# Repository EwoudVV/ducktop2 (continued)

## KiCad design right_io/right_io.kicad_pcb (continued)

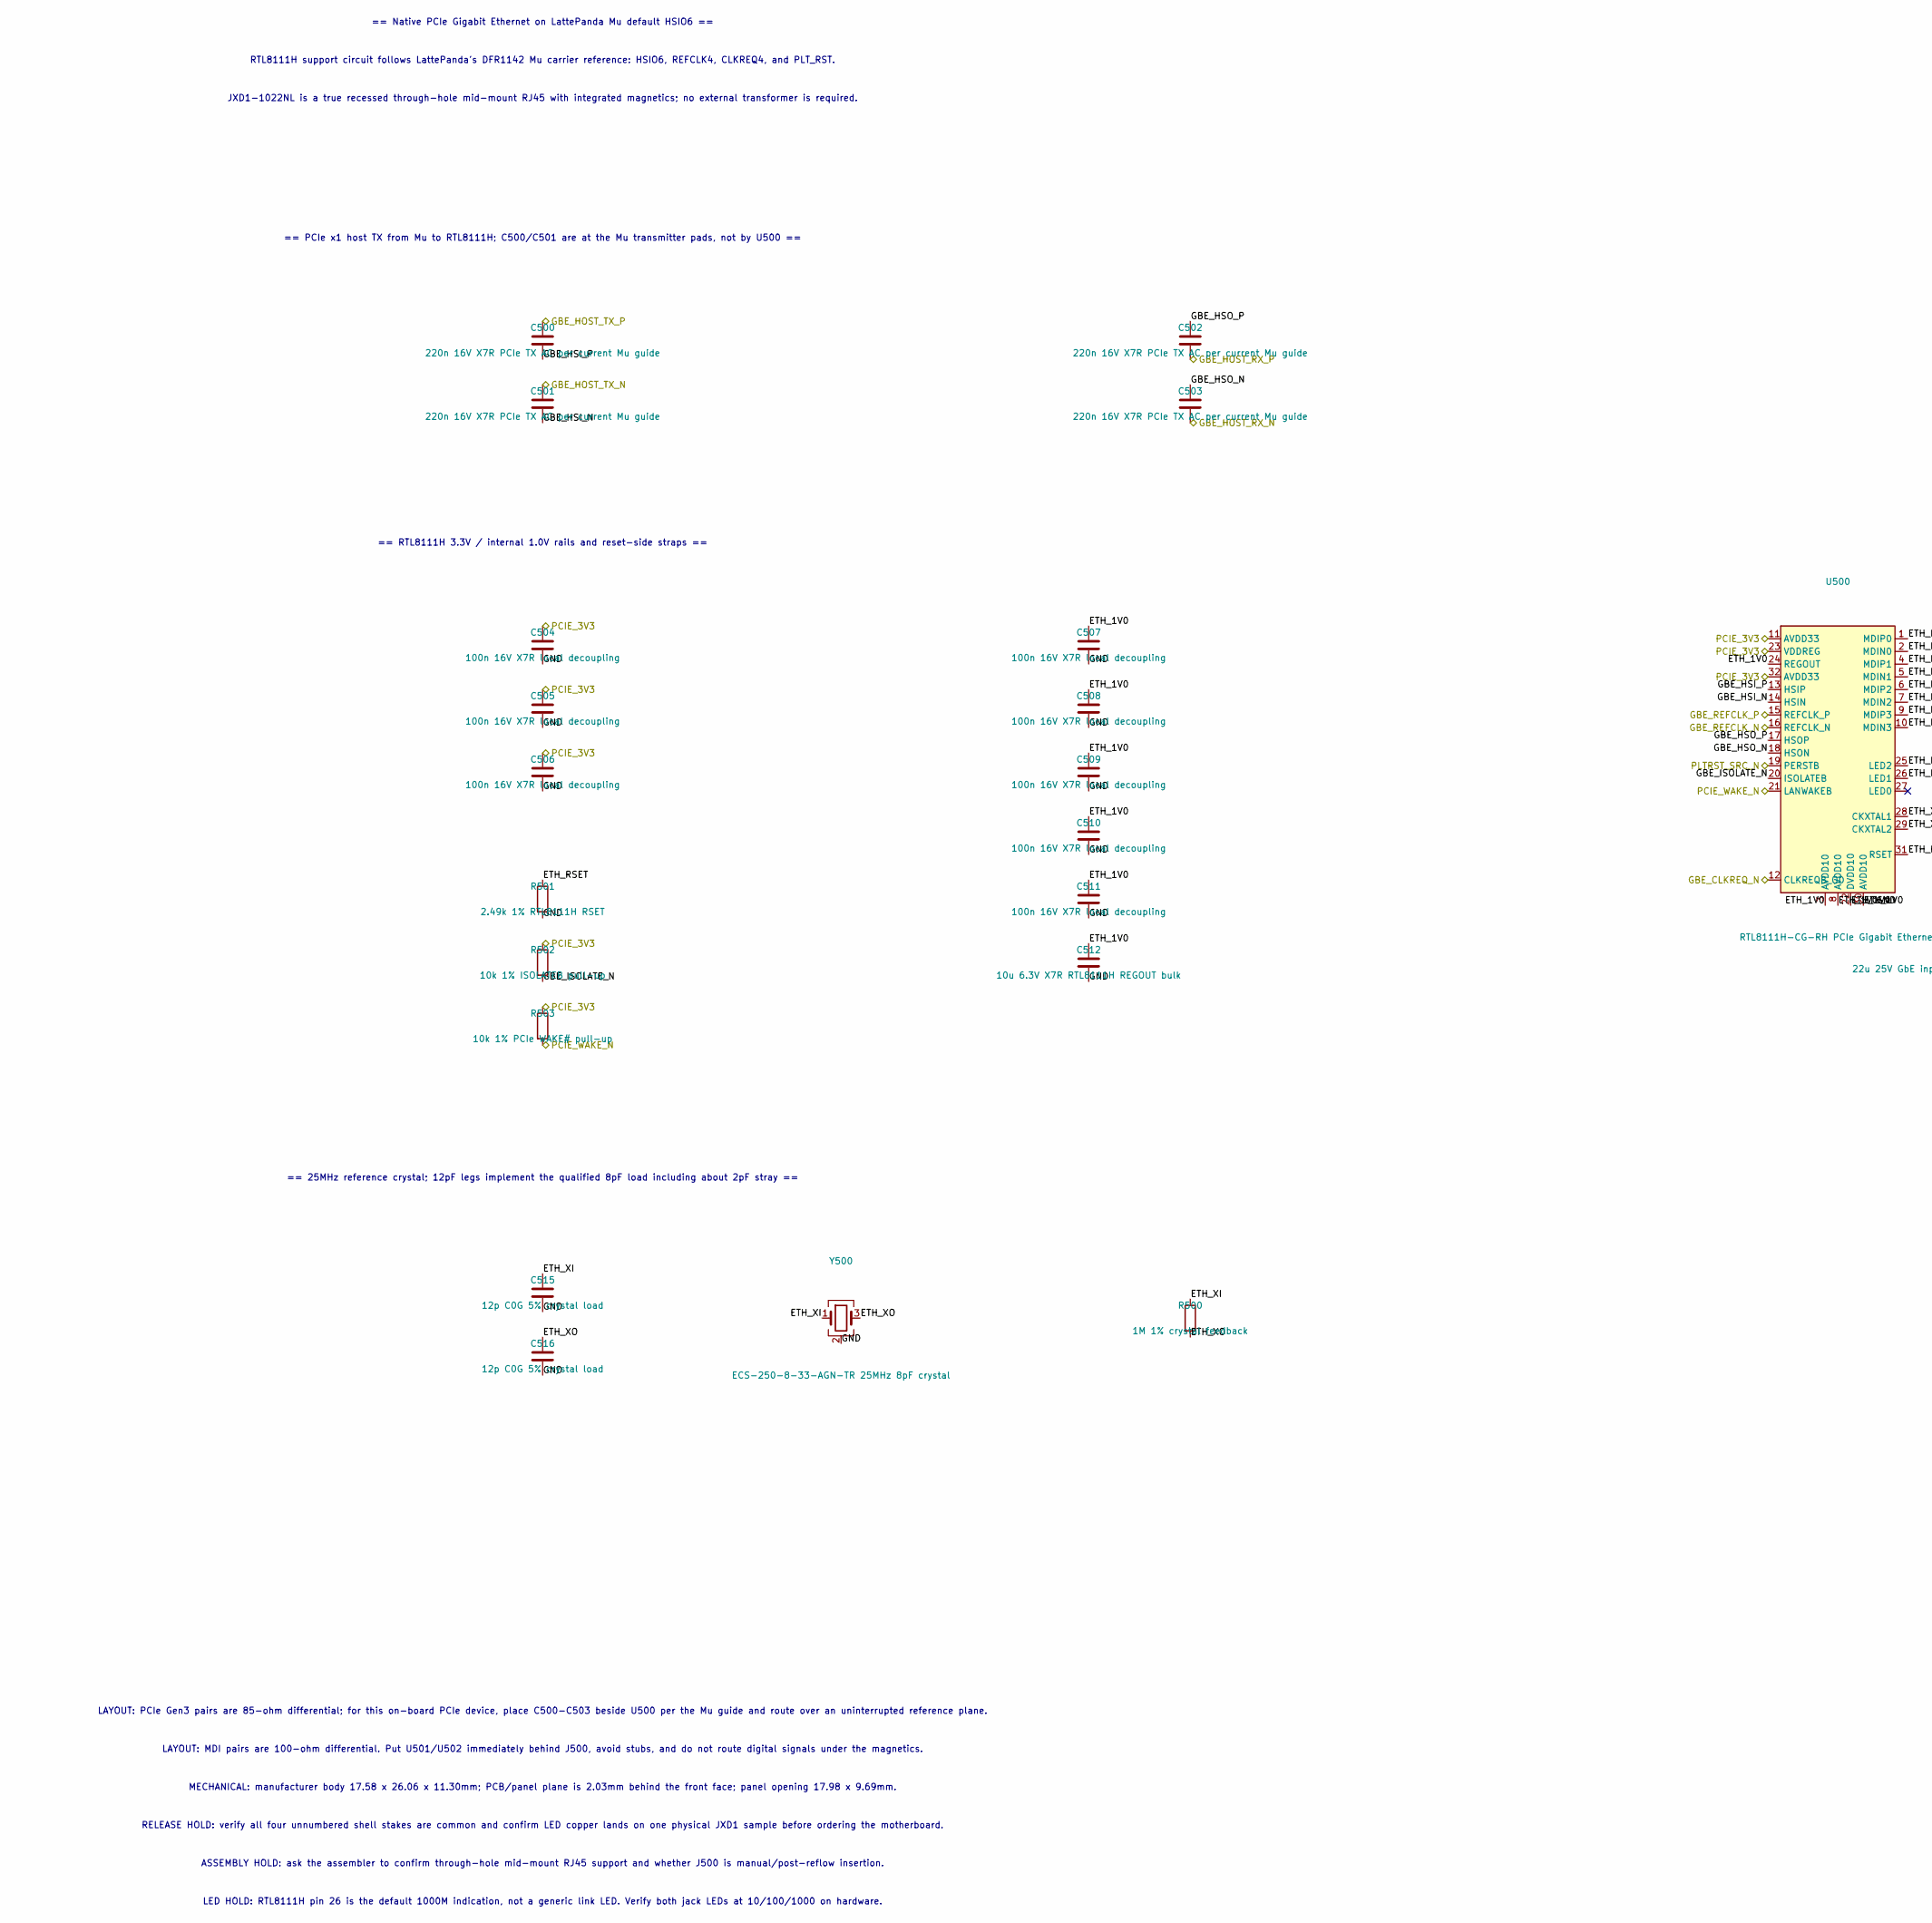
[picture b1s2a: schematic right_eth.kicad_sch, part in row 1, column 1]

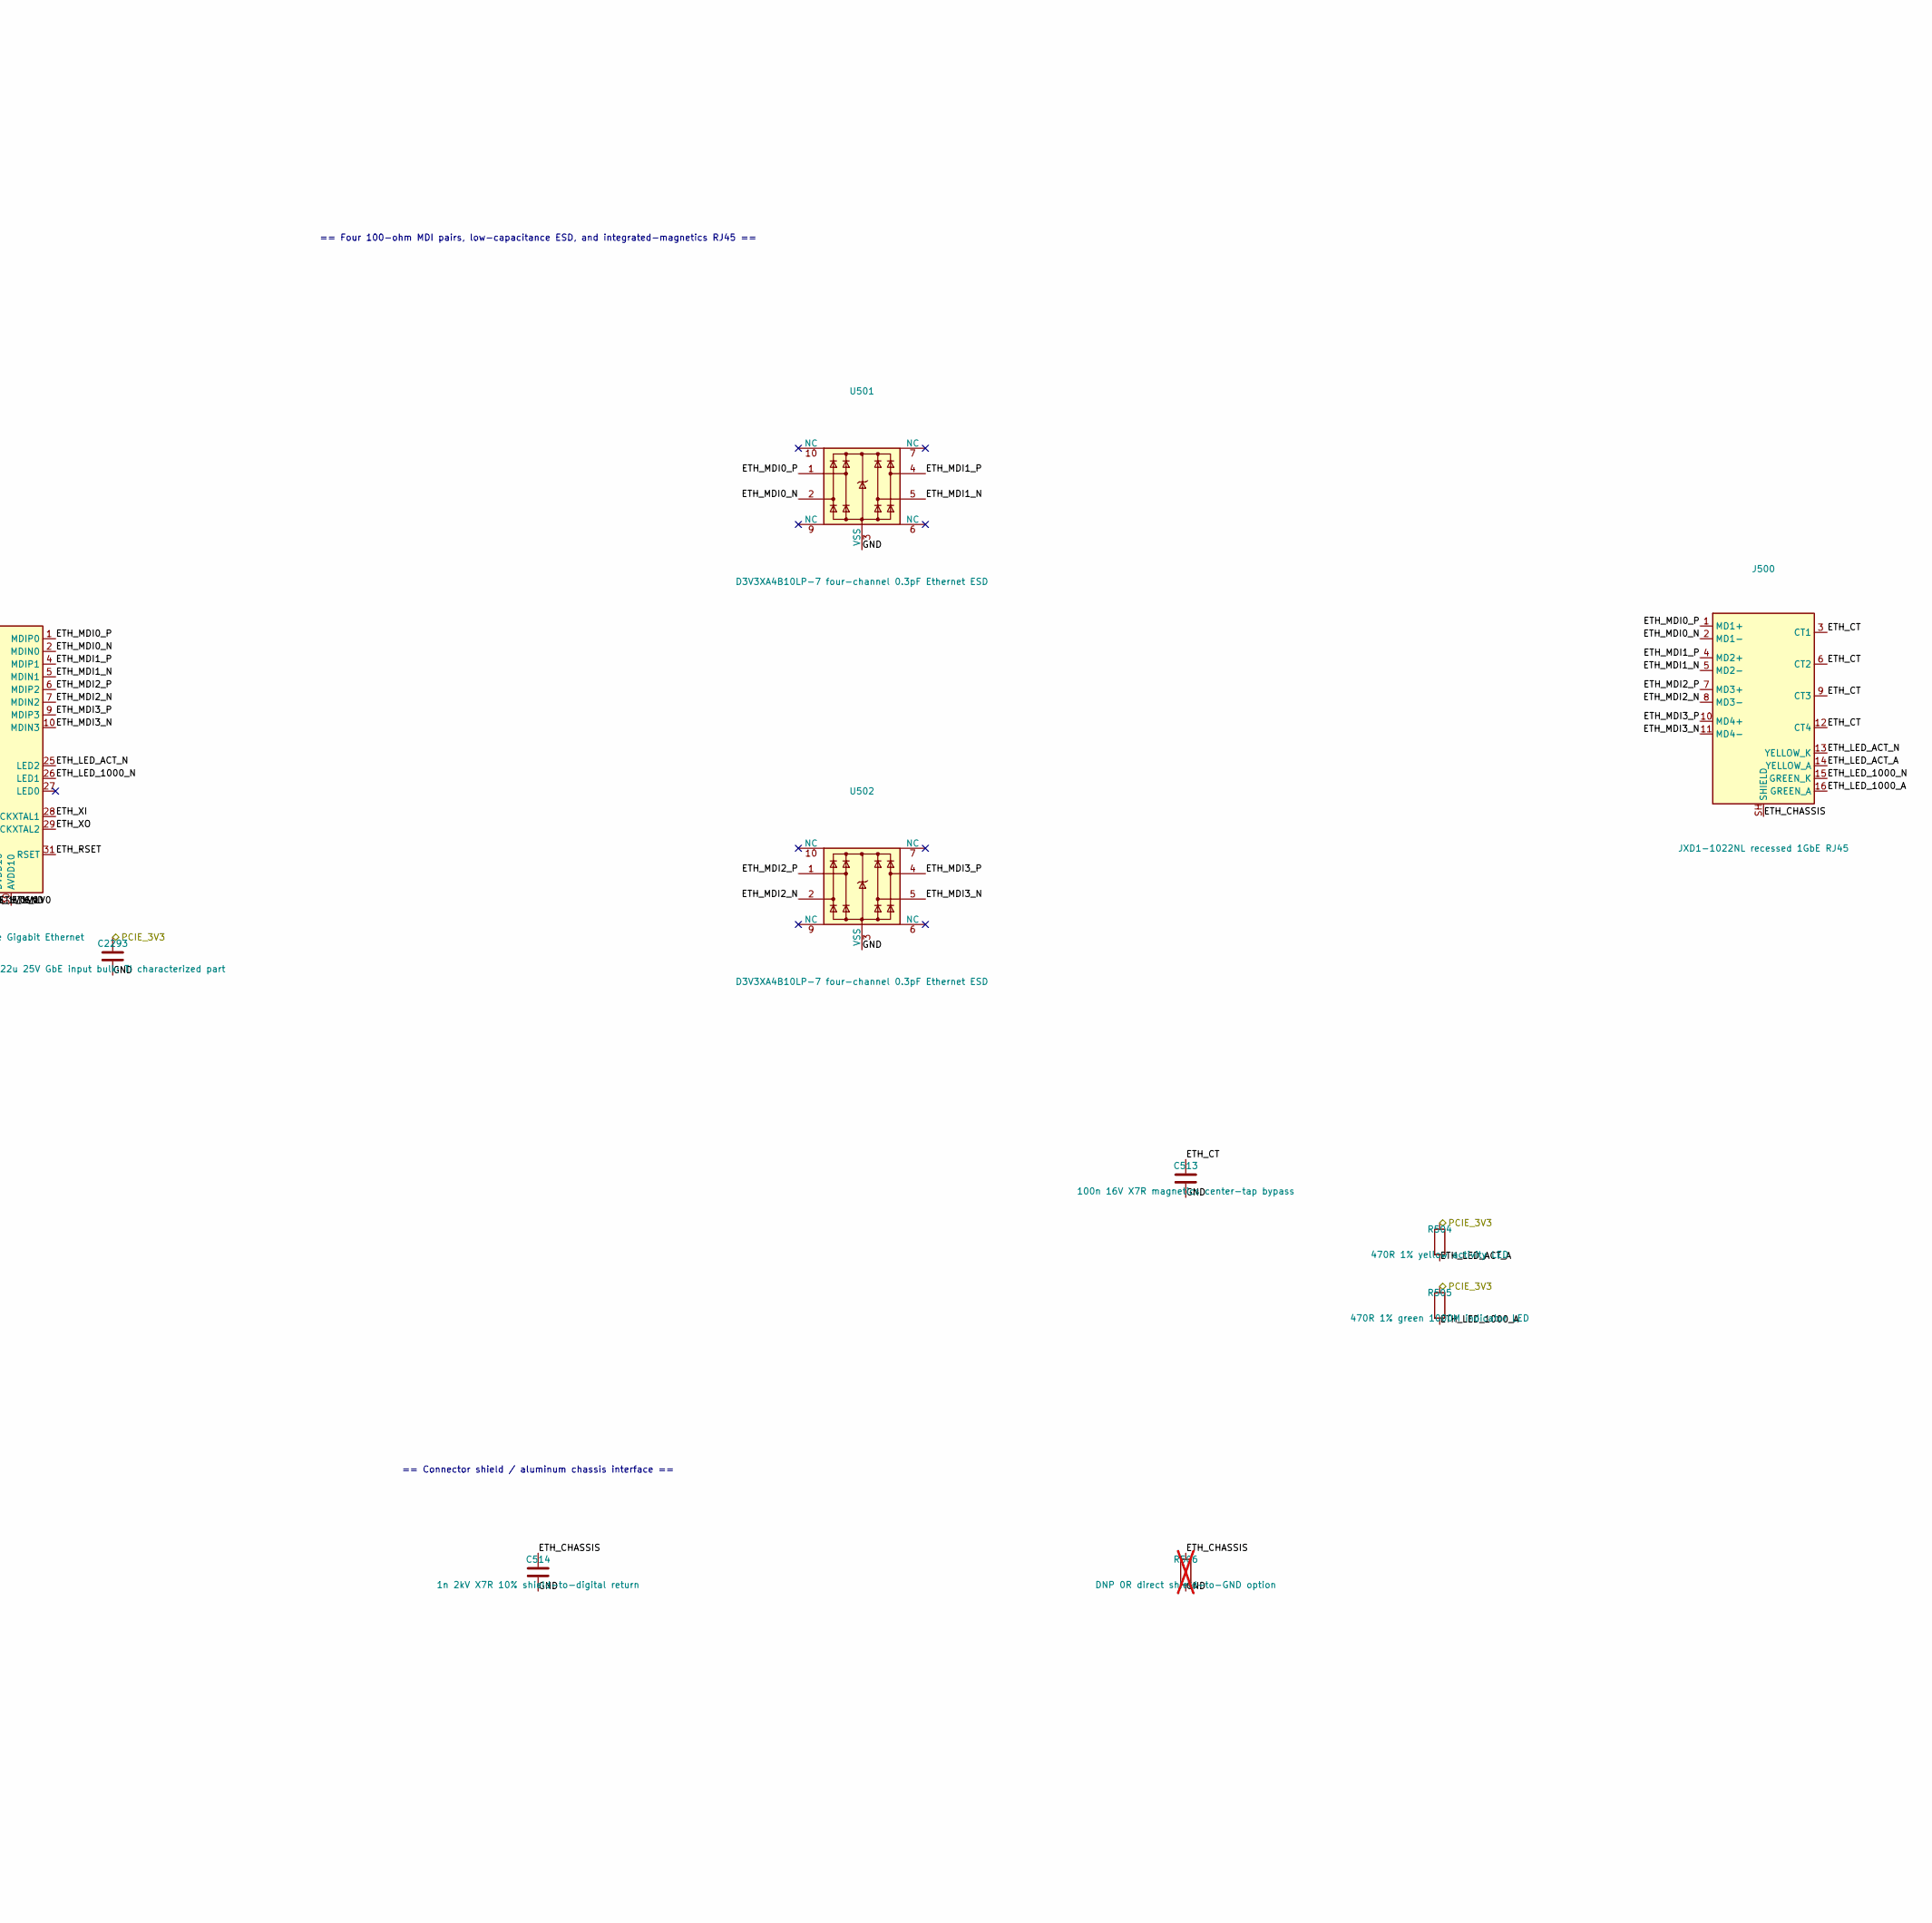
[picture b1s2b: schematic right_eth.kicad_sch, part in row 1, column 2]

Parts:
C500, C501, C502, C503: 220n 16V X7R PCIe TX AC per current Mu guide; C_0402_1005Metric; MPN GRM155R71C224KA12D
C504, C505, C506, C507, C508, C509, C510, C511: 100n 16V X7R local decoupling; C_0402_1005Metric; MPN GRM155R71C104KA88D
C512: 10u 6.3V X7R RTL8111H REGOUT bulk; C_1206_3216Metric; MPN GRM31CR71E106KA12L
C513: 100n 16V X7R magnetics center-tap bypass; C_0402_1005Metric; MPN GRM155R71C104KA88D
C514: 1n 2kV X7R 10% shield-to-digital return; C_1812_4532Metric; MPN C1812C102KGRACTU
C515, C516: 12p C0G 5% crystal load; C_0402_1005Metric; MPN GRM1555C1H120JA01J
C2293: 22u 25V GbE input bulk; TI characterized part; C_1210_3225Metric; MPN GRM32ER71E226KE15L
J500: JXD1-1022NL recessed 1GbE RJ45; JXD1-1022NL_MidMount; MPN JXD1-1022NL
R500: 1M 1% crystal feedback; R_0402_1005Metric; MPN RC0402FR-071ML
R501: 2.49k 1% RTL8111H RSET; R_0402_1005Metric; MPN RC0402FR-072K49L
R502: 10k 1% ISOLATEB pull-up; R_0402_1005Metric; MPN RC0402FR-0710KL
R503: 10k 1% PCIe WAKE# pull-up; R_0402_1005Metric; MPN RC0402FR-0710KL
R504: 470R 1% yellow activity LED; R_0402_1005Metric; MPN RC0402FR-07470RL
R505: 470R 1% green 1000M indicator LED; R_0402_1005Metric; MPN RC0402FR-07470RL
R506: DNP 0R direct shield-to-GND option; R_1206_3216Metric; not fitted
U500: RTL8111H-CG-RH PCIe Gigabit Ethernet; QFN-32-1EP_4x4mm_P0.4mm_EP2.65x2.65mm; MPN RTL8111H-CG-RH
U501, U502: D3V3XA4B10LP-7 four-channel 0.3pF Ethernet ESD; Diodes_UDFN-10_1x2.5mm_P0.5mm; MPN D3V3XA4B10LP-7
Y500: ECS-250-8-33-AGN-TR 25MHz 8pF crystal; Crystal_SMD_3225-4Pin_3.2x2.5mm; MPN ECS-250-8-33-AGN-TR

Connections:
/GBE_CLKREQ_N: U500.12 (CLKREQB_OD); also elsewhere on the board
/GBE_HOST_RX_N: C503.2; also elsewhere on the board
/GBE_HOST_RX_P: C502.2; also elsewhere on the board
/GBE_HOST_TX_N: C501.1; also elsewhere on the board
/GBE_HOST_TX_P: C500.1; also elsewhere on the board
/GBE_REFCLK_N: U500.16 (REFCLK_N); also elsewhere on the board
/GBE_REFCLK_P: U500.15 (REFCLK_P); also elsewhere on the board
/GbE/ETH_1V0: C507.1, C508.1, C509.1, C510.1, C511.1, C512.1, U500.3 (AVDD10), U500.8 (AVDD10), U500.22 (DVDD10), U500.24 (REGOUT), U500.30 (AVDD10)
/GbE/ETH_CHASSIS: C514.1, J500.SH (SHIELD), R506.1
/GbE/ETH_CT: C513.1, J500.3 (CT1), J500.6 (CT2), J500.9 (CT3), J500.12 (CT4)
/GbE/ETH_LED_1000_A: J500.16 (GREEN_A), R505.2
/GbE/ETH_LED_1000_N: J500.15 (GREEN_K), U500.26 (LED1)
/GbE/ETH_LED_ACT_A: J500.14 (YELLOW_A), R504.2
/GbE/ETH_LED_ACT_N: J500.13 (YELLOW_K), U500.25 (LED2)
/GbE/ETH_MDI0_N: J500.2 (MD1-), U500.2 (MDIN0), U501.2
/GbE/ETH_MDI0_P: J500.1 (MD1+), U500.1 (MDIP0), U501.1
/GbE/ETH_MDI1_N: J500.5 (MD2-), U500.5 (MDIN1), U501.5
/GbE/ETH_MDI1_P: J500.4 (MD2+), U500.4 (MDIP1), U501.4
/GbE/ETH_MDI2_N: J500.8 (MD3-), U500.7 (MDIN2), U502.2
/GbE/ETH_MDI2_P: J500.7 (MD3+), U500.6 (MDIP2), U502.1
/GbE/ETH_MDI3_N: J500.11 (MD4-), U500.10 (MDIN3), U502.5
/GbE/ETH_MDI3_P: J500.10 (MD4+), U500.9 (MDIP3), U502.4
/GbE/ETH_RSET: R501.1, U500.31 (RSET)
/GbE/ETH_XI: C515.1, R500.1, U500.28 (CKXTAL1), Y500.1
/GbE/ETH_XO: C516.1, R500.2, U500.29 (CKXTAL2), Y500.3
/GbE/GBE_HSI_N: C501.2, U500.14 (HSIN)
/GbE/GBE_HSI_P: C500.2, U500.13 (HSIP)
/GbE/GBE_HSO_N: C503.1, U500.18 (HSON)
/GbE/GBE_HSO_P: C502.1, U500.17 (HSOP)
/GbE/GBE_ISOLATE_N: R502.2, U500.20 (ISOLATEB)
/PCIE_3V3: C504.1, C505.1, C506.1, C2293.1, R502.1, R503.1, R504.1, R505.1, U500.11 (AVDD33), U500.23 (VDDREG), U500.32 (AVDD33); also elsewhere on the board
/PCIE_WAKE_N: R503.2, U500.21 (LANWAKEB); also elsewhere on the board
/PLTRST_SRC_N: U500.19 (PERSTB); also elsewhere on the board
GND: C504.2, C505.2, C506.2, C507.2, C508.2, C509.2, C510.2, C511.2, C512.2, C513.2, C514.2, C515.2, C516.2, C2293.2, R501.2, R506.2, U500.33 (GND), U501.3 (VSS), U501.8 (VSS), U502.3 (VSS), U502.8 (VSS), Y500.2 (G), Y500.4 (G); also elsewhere on the board

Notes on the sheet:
== Native PCIe Gigabit Ethernet on LattePanda Mu default HSIO6 ==
RTL8111H support circuit follows LattePanda's DFR1142 Mu carrier reference: HSIO6, REFCLK4, CLKREQ4, and PLT_RST.
JXD1-1022NL is a true recessed through-hole mid-mount RJ45 with integrated magnetics; no external transformer is required.
== PCIe x1 host TX from Mu to RTL8111H; C500/C501 are at the Mu transmitter pads, not by U500 ==
== RTL8111H 3.3V / internal 1.0V rails and reset-side straps ==
== 25MHz reference crystal; 12pF legs implement the qualified 8pF load including about 2pF stray ==
== Four 100-ohm MDI pairs, low-capacitance ESD, and integrated-magnetics RJ45 ==
== Connector shield / aluminum chassis interface ==
LAYOUT: PCIe Gen3 pairs are 85-ohm differential; for this on-board PCIe device, place C500-C503 beside U500 per the Mu guide and route over an uninterrupted reference plane.
LAYOUT: MDI pairs are 100-ohm differential. Put U501/U502 immediately behind J500, avoid stubs, and do not route digital signals under the magnetics.
MECHANICAL: manufacturer body 17.58 x 26.06 x 11.30mm; PCB/panel plane is 2.03mm behind the front face; panel opening 17.98 x 9.69mm.
RELEASE HOLD: verify all four unnumbered shell stakes are common and confirm LED copper lands on one physical JXD1 sample before ordering the motherboard.
ASSEMBLY HOLD: ask the assembler to confirm through-hole mid-mount RJ45 support and whether J500 is manual/post-reflow insertion.
LED HOLD: RTL8111H pin 26 is the default 1000M indication, not a generic link LED. Verify both jack LEDs at 10/100/1000 on hardware.

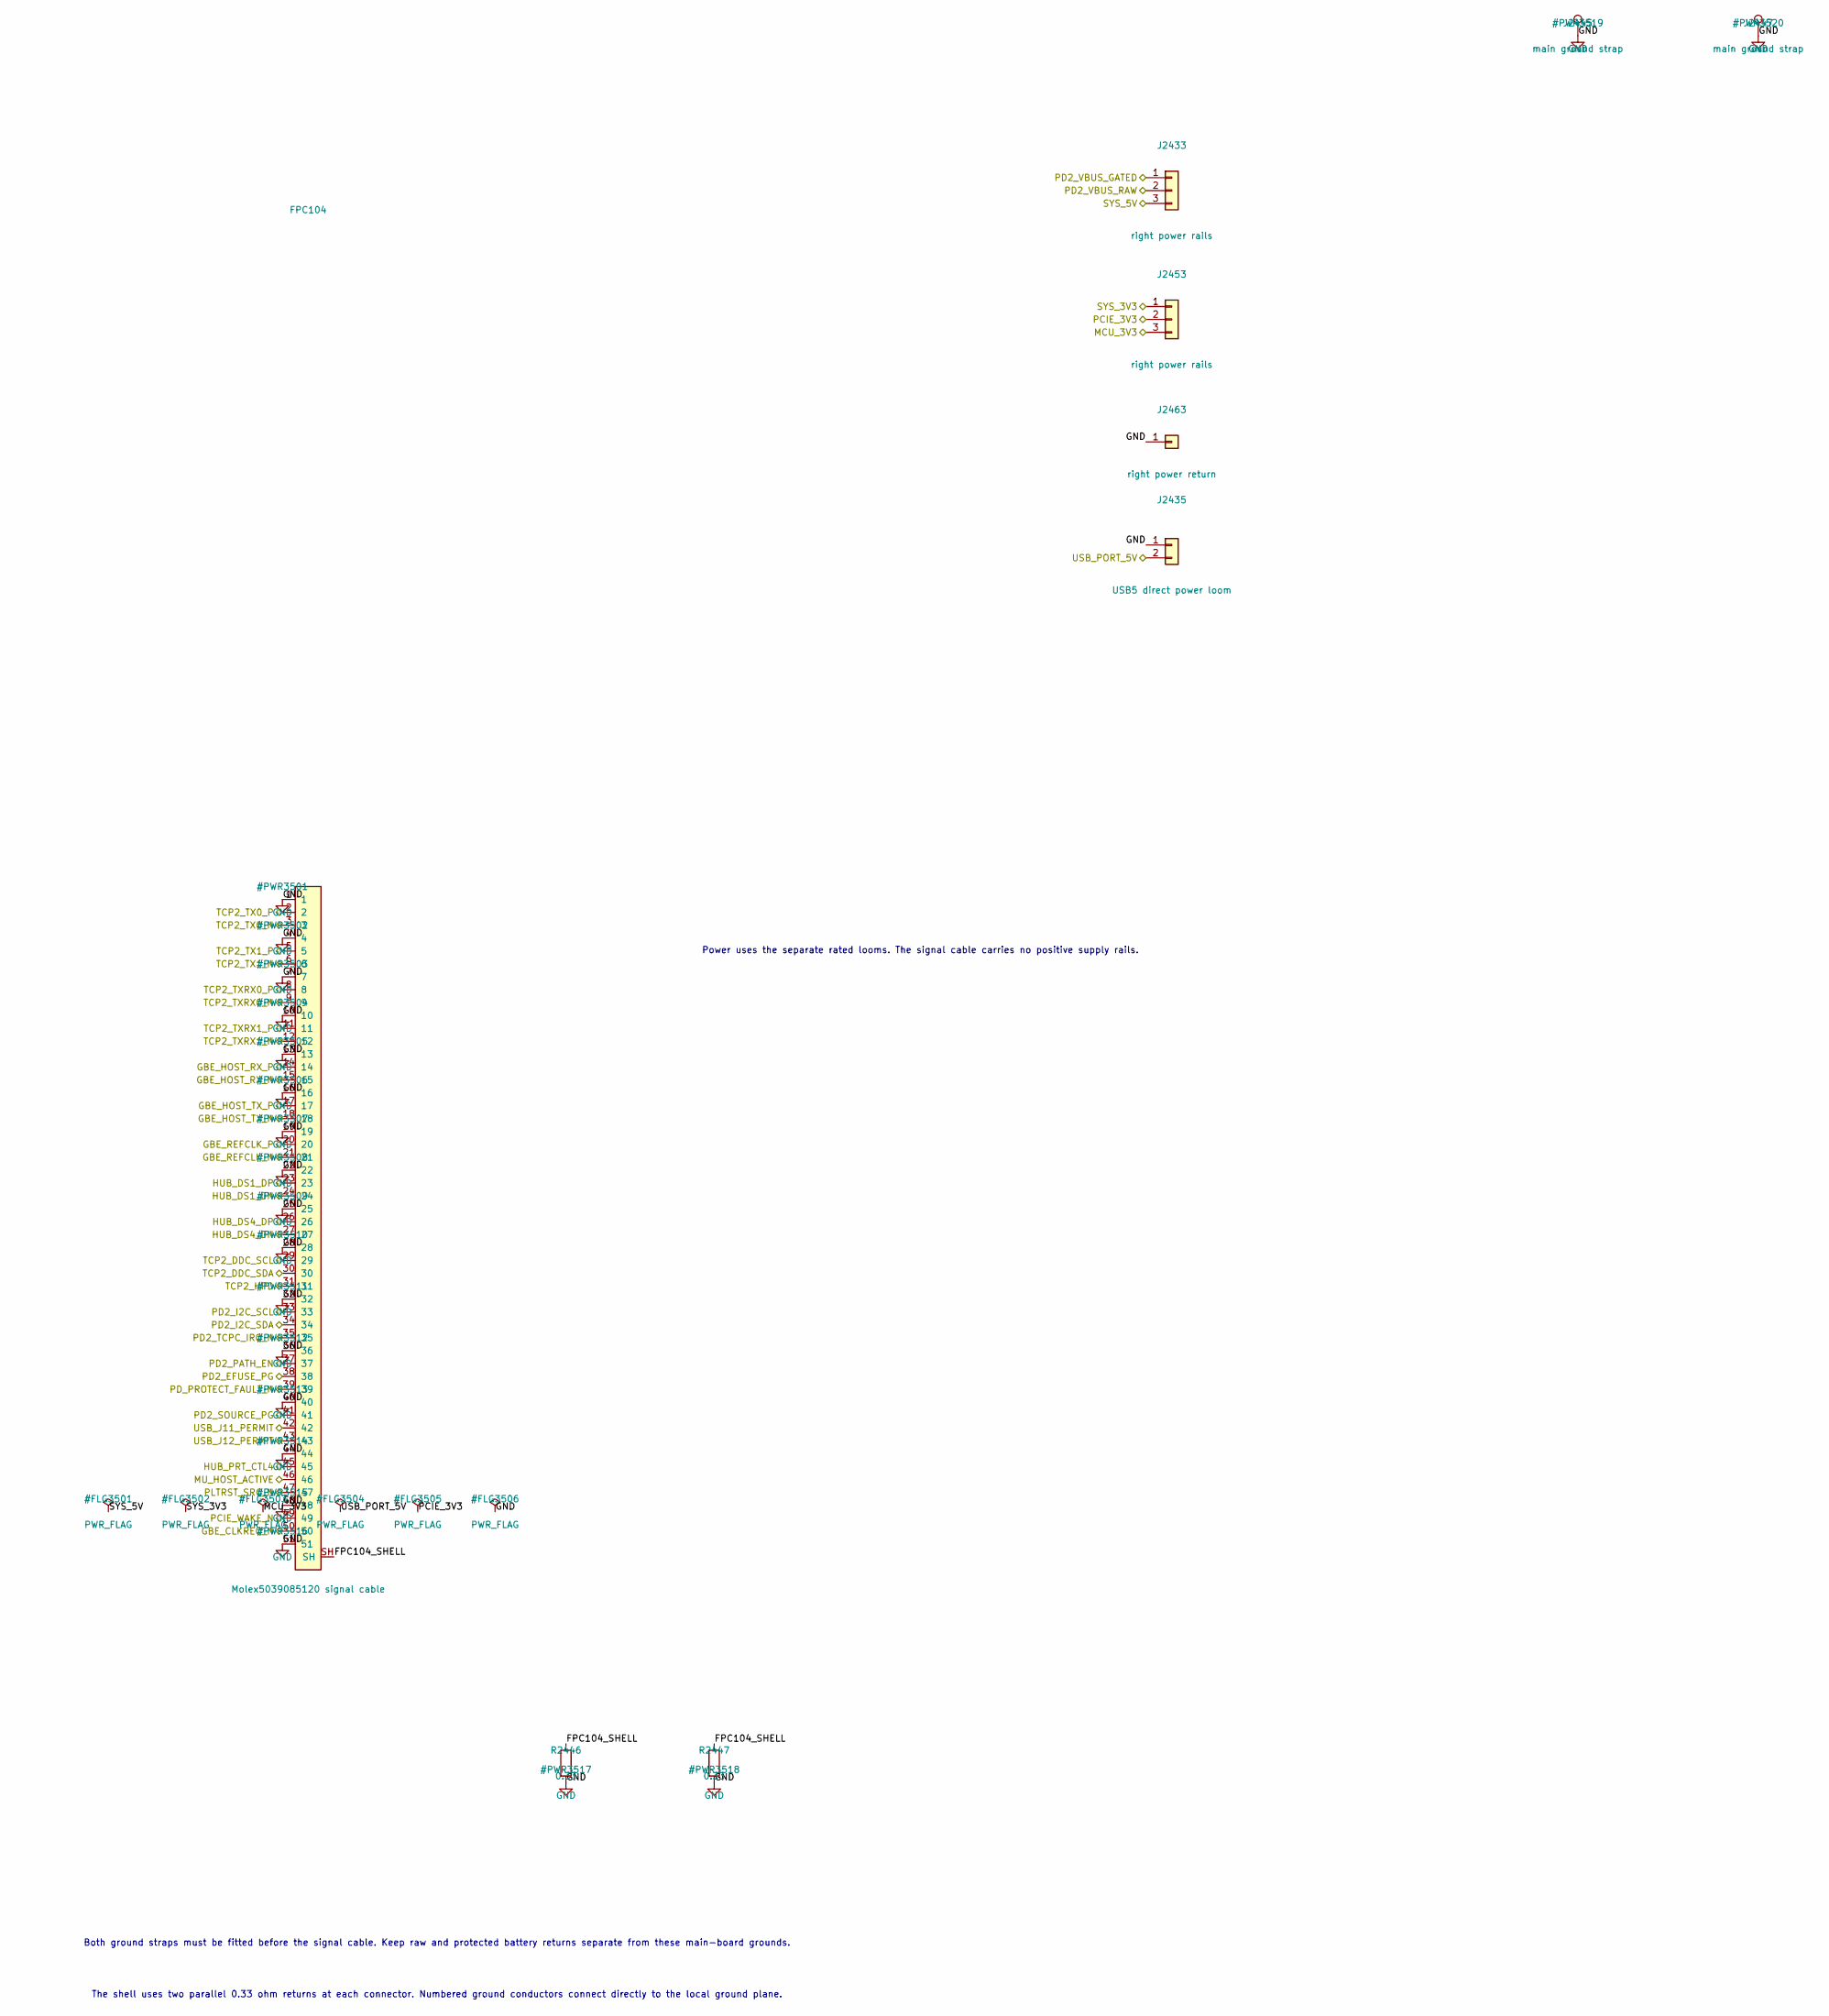
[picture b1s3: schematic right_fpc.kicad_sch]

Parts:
FPC104: Molex5039085120 signal cable; Molex_5039085120_1x51_P0.50mm_Horizontal; MPN 5039085120
J2433, J2453: right power rails; WAGO_2060_453_SMD; MPN 2060-453/998-404
J2435: USB5 direct power loom; AMASS_XT30PW-F30_G_Y; MPN XT30PW-F30.G.Y
J2445, J2447: main ground strap; SolderWirePad_1x01_SMD_5x10mm
J2463: right power return; WAGO_2060_451_SMD; MPN 2060-451/998-404
R2446, R2447: 0.33; R_0603_1608Metric; MPN ERJ3RQFR33V

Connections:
/FPC-2 (to Center)/FPC104_SHELL: FPC104.SH, R2446.1, R2447.1
/GBE_CLKREQ_N: FPC104.50; also elsewhere on the board
/GBE_HOST_RX_N: FPC104.15; also elsewhere on the board
/GBE_HOST_RX_P: FPC104.14; also elsewhere on the board
/GBE_HOST_TX_N: FPC104.18; also elsewhere on the board
/GBE_HOST_TX_P: FPC104.17; also elsewhere on the board
/GBE_REFCLK_N: FPC104.21; also elsewhere on the board
/GBE_REFCLK_P: FPC104.20; also elsewhere on the board
/HUB_DS1_DN: FPC104.24; also elsewhere on the board
/HUB_DS1_DP: FPC104.23; also elsewhere on the board
/HUB_DS4_DN: FPC104.27; also elsewhere on the board
/HUB_DS4_DP: FPC104.26; also elsewhere on the board
/HUB_PRT_CTL4: FPC104.45; also elsewhere on the board
/MCU_3V3: J2453.3; also elsewhere on the board
/MU_HOST_ACTIVE: FPC104.46; also elsewhere on the board
/PCIE_3V3: J2453.2; also elsewhere on the board
/PCIE_WAKE_N: FPC104.49; also elsewhere on the board
/PD2_EFUSE_PG: FPC104.38; also elsewhere on the board
/PD2_I2C_SCL: FPC104.33; also elsewhere on the board
/PD2_I2C_SDA: FPC104.34; also elsewhere on the board
/PD2_PATH_EN: FPC104.37; also elsewhere on the board
/PD2_SOURCE_PG: FPC104.41; also elsewhere on the board
/PD2_TCPC_IRQ_N: FPC104.35; also elsewhere on the board
/PD2_VBUS_GATED: J2433.1; also elsewhere on the board
/PD2_VBUS_RAW: J2433.2; also elsewhere on the board
/PD_PROTECT_FAULT_N: FPC104.39; also elsewhere on the board
/PLTRST_SRC_N: FPC104.47; also elsewhere on the board
/SYS_3V3: J2453.1; also elsewhere on the board
/SYS_5V: J2433.3; also elsewhere on the board
/TCP2_DDC_SCL: FPC104.29; also elsewhere on the board
/TCP2_DDC_SDA: FPC104.30; also elsewhere on the board
/TCP2_HPD: FPC104.31; also elsewhere on the board
/TCP2_TX0_N: FPC104.3; also elsewhere on the board
/TCP2_TX0_P: FPC104.2; also elsewhere on the board
/TCP2_TX1_N: FPC104.6; also elsewhere on the board
/TCP2_TX1_P: FPC104.5; also elsewhere on the board
/TCP2_TXRX0_N: FPC104.9; also elsewhere on the board
/TCP2_TXRX0_P: FPC104.8; also elsewhere on the board
/TCP2_TXRX1_N: FPC104.12; also elsewhere on the board
/TCP2_TXRX1_P: FPC104.11; also elsewhere on the board
/USB_J11_PERMIT: FPC104.42; also elsewhere on the board
/USB_J12_PERMIT: FPC104.43; also elsewhere on the board
/USB_PORT_5V: J2435.2; also elsewhere on the board
GND: FPC104.1, FPC104.4, FPC104.7, FPC104.10, FPC104.13, FPC104.16, FPC104.19, FPC104.22, FPC104.25, FPC104.28, FPC104.32, FPC104.36, FPC104.40, FPC104.44, FPC104.48, FPC104.51, J2435.1, J2445.1, J2447.1, J2463.1, R2446.2, R2447.2; also elsewhere on the board

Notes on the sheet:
Power uses the separate rated looms. The signal cable carries no positive supply rails.
Both ground straps must be fitted before the signal cable. Keep raw and protected battery returns separate from these main-board grounds.
The shell uses two parallel 0.33 ohm returns at each connector. Numbered ground conductors connect directly to the local ground plane.

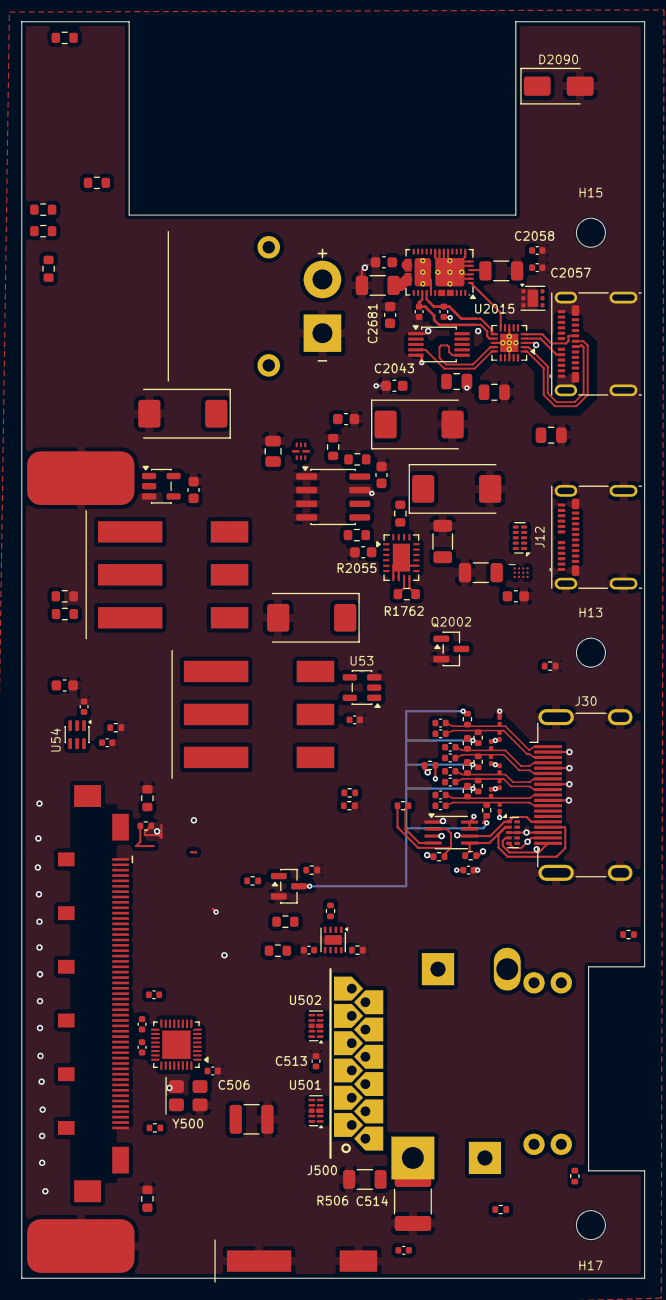
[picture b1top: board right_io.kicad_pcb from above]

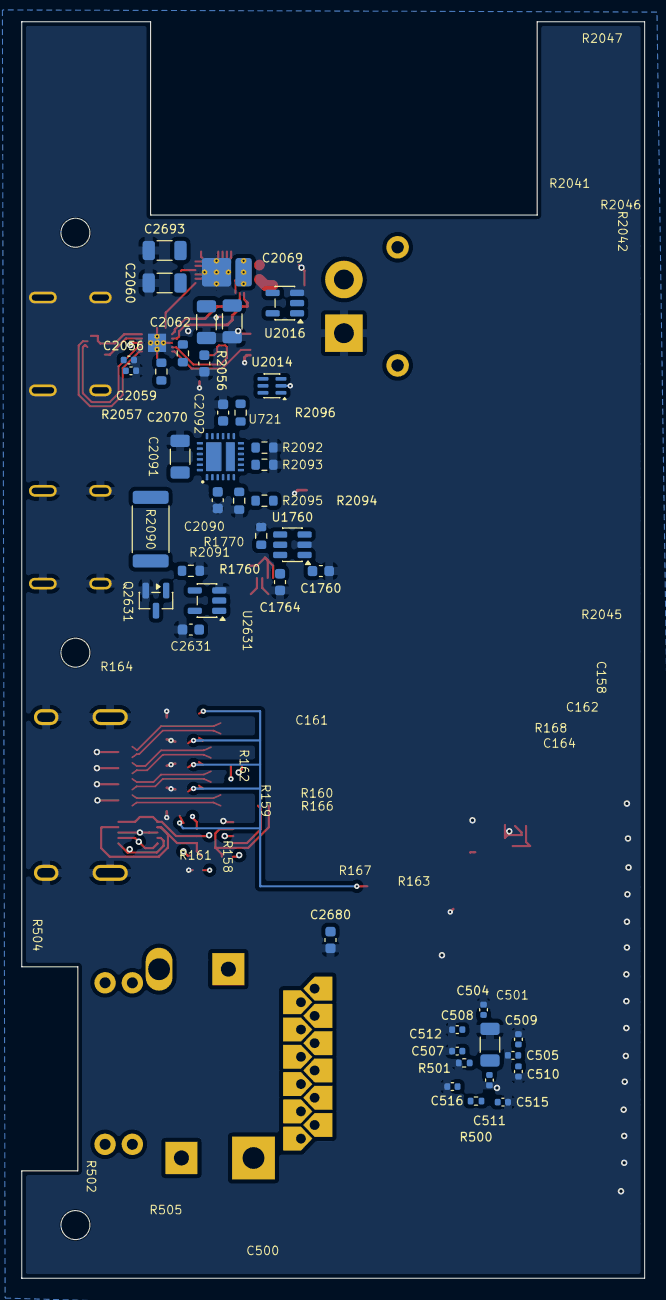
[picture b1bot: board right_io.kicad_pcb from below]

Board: 8 copper layers, 58.0 x 117.0 mm, 174 parts (42 on the bottom side), 128 nets.
